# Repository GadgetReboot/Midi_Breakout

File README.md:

# Midi_Breakout
Midi In/Out/Thru Breakout PCB 
<br><br><br><br>
Configured for 5V logic levels

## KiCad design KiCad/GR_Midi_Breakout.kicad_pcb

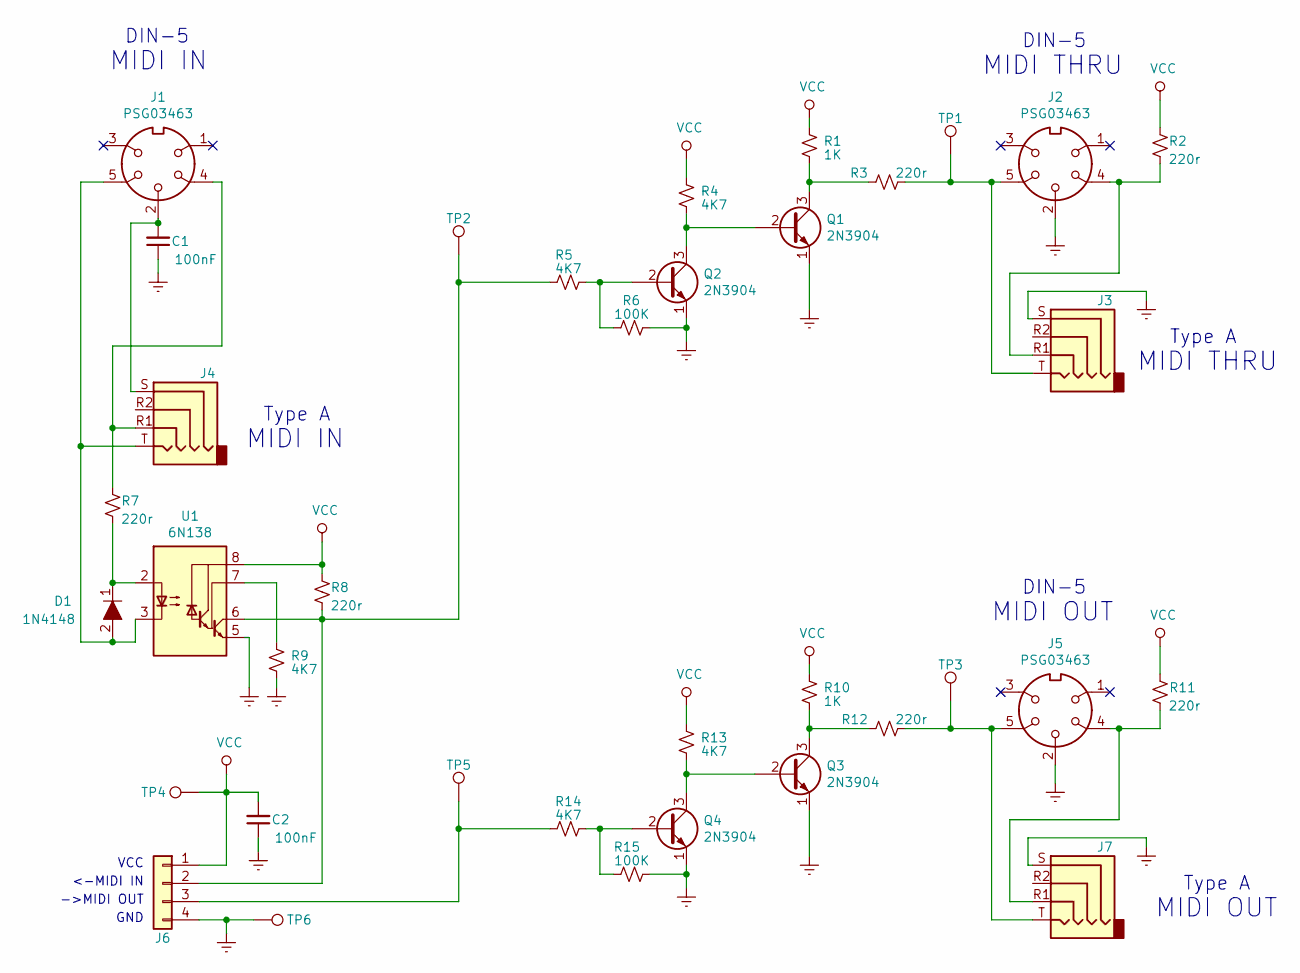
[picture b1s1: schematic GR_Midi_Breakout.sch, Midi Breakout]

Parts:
C1, C2: 100nF; C_Disc_D3.8mm_W2.6mm_P2.50mm
D1: 1N4148; D_DO-35_SOD27_P10.16mm_Horizontal; MPN 1N4148; Digi-Key_PN 1N4148FS-ND
J1, J2, J5: PSG03463; DIN5
J3, J4, J7: AudioJack4; PJ320A
J6: Conn_01x04; PinHeader_1x04_P2.54mm_Vertical
Q1, Q2, Q3, Q4: 2N3904; TO-92_Inline_Wide
R1, R10: 1K; R_Axial_DIN0207_L6.3mm_D2.5mm_P10.16mm_Horizontal
R2, R3, R7, R8, R11, R12: 220r; R_Axial_DIN0207_L6.3mm_D2.5mm_P10.16mm_Horizontal
R4, R5, R9, R13, R14: 4K7; R_Axial_DIN0207_L6.3mm_D2.5mm_P10.16mm_Horizontal
R6, R15: 100K; R_Axial_DIN0207_L6.3mm_D2.5mm_P10.16mm_Horizontal
TP1, TP2, TP3, TP4, TP5, TP6: TestPoint; TestPoint_Loop_D1.80mm_Drill1.0mm_Beaded
U1: 6N138; DIP-8_W7.62mm_Socket_LongPads

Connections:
GNDREF: C1.1, C2.1, J2.2, J3.S, J5.2, J6.4, J7.S, Q1.1 (E), Q2.1 (E), Q3.1 (E), Q4.1 (E), R6.1, R9.1, R15.1, TP6.1, U1.5 (GND)
unnamed: C1.2, J1.2, J4.S
unnamed: D1.1, R7.2, U1.2 (C1)
unnamed: D1.2, J1.5, J4.T, U1.3 (C2)
unnamed: J1.4, J4.R1, R7.1
unnamed: J2.4, J3.R1, R2.2
unnamed: J2.5, J3.T, R3.1, TP1.1
unnamed: J5.4, J7.R1, R11.2
unnamed: J5.5, J7.T, R12.1, TP3.1
unnamed: J6.2, R5.1, R8.2, TP2.1, U1.6 (VO2)
unnamed: J6.3, R14.1, TP5.1
unnamed: Q1.2 (B), Q2.3 (C), R4.1
unnamed: Q1.3 (C), R1.1, R3.2
unnamed: Q2.2 (B), R5.2, R6.2
unnamed: Q3.2 (B), Q4.3 (C), R13.1
unnamed: Q3.3 (C), R10.1, R12.2
unnamed: Q4.2 (B), R14.2, R15.2
unnamed: R9.2, U1.7 (VO1)
VCC: C2.2, J6.1, R1.2, R2.1, R4.2, R8.1, R10.2, R11.1, R13.2, TP4.1, U1.8 (VCC)

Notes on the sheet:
VCC
MIDI THRU
->MIDI OUT
<-MIDI IN
GND
DIN-5
Type A
MIDI IN
MIDI OUT

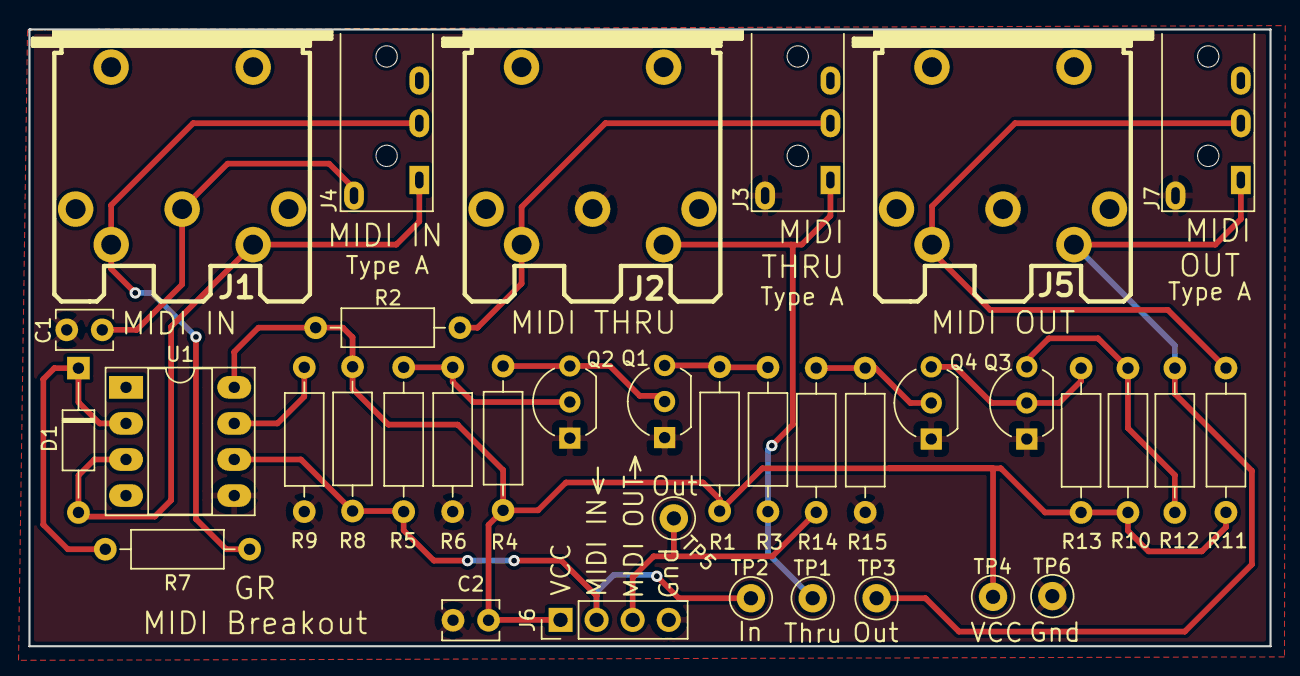
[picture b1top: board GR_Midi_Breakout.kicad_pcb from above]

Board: 2 copper layers, 87.4 x 43.4 mm, 36 parts (0 on the bottom side), 19 nets.
